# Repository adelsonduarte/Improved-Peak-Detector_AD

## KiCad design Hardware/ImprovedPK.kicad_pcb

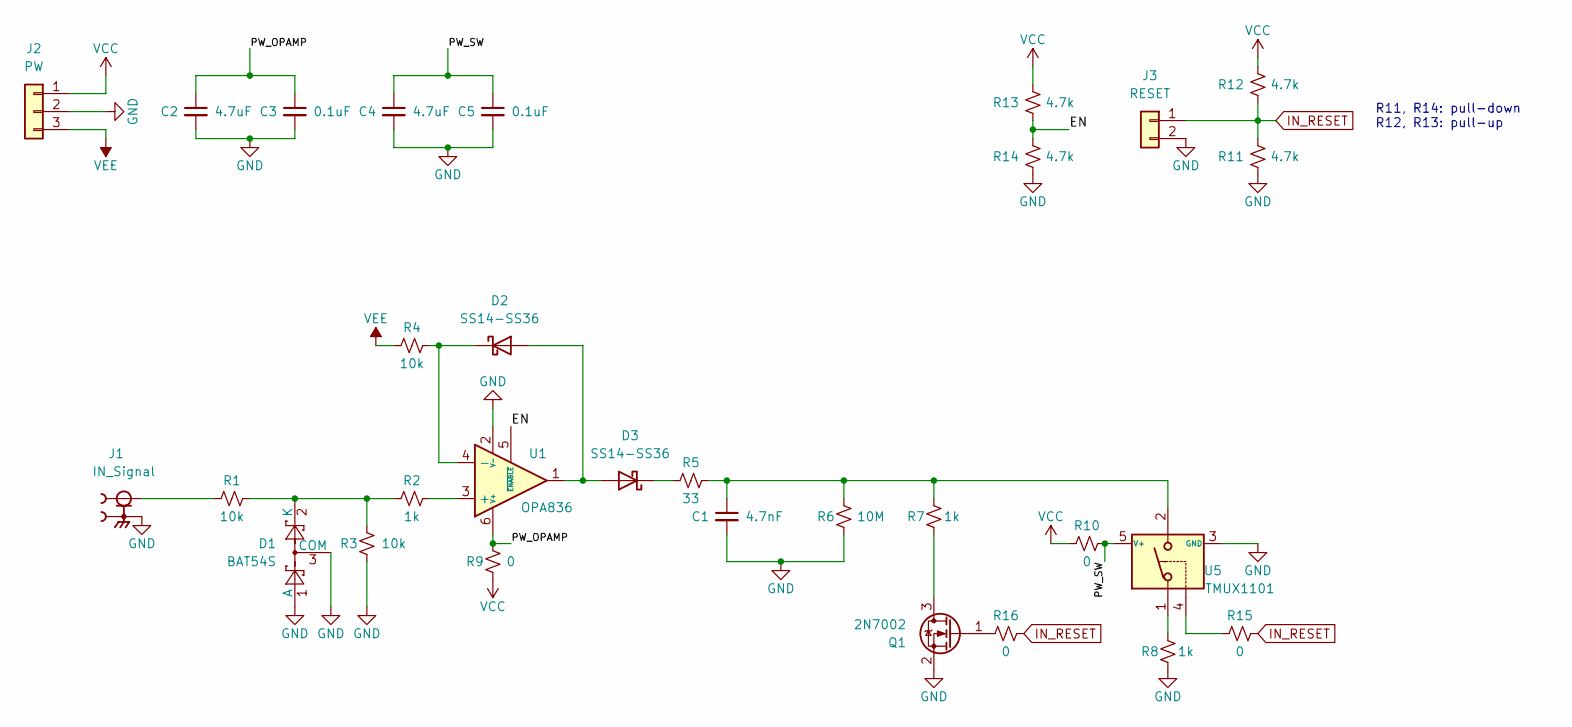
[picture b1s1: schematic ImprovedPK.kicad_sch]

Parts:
C1: 4.7nF; C_0805_2012Metric_Pad1.18x1.45mm_HandSolder
C2: 4.7uF; R_0805_2012Metric_Pad1.20x1.40mm_HandSolder
C3, C5: 0.1uF; C_0805_2012Metric_Pad1.18x1.45mm_HandSolder
C4: 4.7uF; C_0805_2012Metric_Pad1.18x1.45mm_HandSolder
D1: BAT54S; SOT-23
D2, D3: SS14-SS36; D_SMA
J1: IN_Signal; LINX_CONSMA020.062-G; PARTREV A
J2: PW; PinHeader_1x03_P2.54mm_Vertical
J3: RESET; PinHeader_1x02_P2.54mm_Vertical
Q1: 2N7002; SOT-23
R1, R3, R4: 10k; R_0805_2012Metric_Pad1.20x1.40mm_HandSolder
R2, R7, R8: 1k; R_0805_2012Metric_Pad1.20x1.40mm_HandSolder
R5: 33; R_0805_2012Metric_Pad1.20x1.40mm_HandSolder
R6: 10M; R_0805_2012Metric_Pad1.20x1.40mm_HandSolder
R9, R10, R15, R16: 0; R_0805_2012Metric_Pad1.20x1.40mm_HandSolder
R11, R12, R13, R14: 4.7k; R_0805_2012Metric_Pad1.20x1.40mm_HandSolder
U1: OPA836; TSOT-23-6
U5: TMUX1101; SOT-23-5

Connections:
/EN: R13.2, R14.1, U1.5 (~ENABLE)
/PW_OPAMP: C2.1, C3.1, R9.2, U1.6 (V+)
/PW_SW: C4.1, C5.1, R10.2; also elsewhere on the board
GND: C1.2, C2.2, C3.2, C4.2, C5.2, D1.1 (A), D1.3 (COM), J1.S1, J2.2, J3.2, Q1.2 (S), R3.1, R6.1, R8.1, R11.1, R14.2, U1.2 (V-); also elsewhere on the board
IN_RESET: J3.1, R11.2, R12.1, R15.2, R16.2
unnamed 5: C1.1, R5.2, R6.2, R7.2; also elsewhere on the board
unnamed: D1.2 (K), R1.2, R2.1, R3.2
unnamed: D2.2 (A), D3.2 (A), U1.1
unnamed: D2.1 (K), R4.2, U1.4 (-)
unnamed: D3.1 (K), R5.1
unnamed: J1.1, R1.1
unnamed: Q1.3 (D), R7.1
unnamed: Q1.1 (G), R16.1
unnamed 13: R8.2; also elsewhere on the board
unnamed 14: R15.1; also elsewhere on the board
unnamed: R2.2, U1.3 (+)
VCC: J2.1, R9.1, R10.1, R12.2, R13.1
VEE: J2.3, R4.1

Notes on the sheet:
R11, R14: pull-down R12, R13: pull-up

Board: 2 copper layers, 30 parts (0 on the bottom side), 18 nets, no tracks yet.

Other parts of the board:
U2: TMUX1101; SOT-23-5

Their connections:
/PW_SW: U2.5 (V+); also elsewhere on the board
GND: U2.3 (GND); also elsewhere on the board
unnamed 5: U2.2; also elsewhere on the board
unnamed 13: U2.1; also elsewhere on the board
unnamed 14: U2.4; also elsewhere on the board

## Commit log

2024-02-09 schematics
